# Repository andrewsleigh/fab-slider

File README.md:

# Fab Slider

A fab-able DIY motorised camera slider

* [The (Arduino Nano) microcontroller, user controls and TMC2130 stepper driver are all integrated onto one board here](boards/driver-arduino-shield/v3)
* [3D and 2D files for the assembly are all here](3d-parts/v1)
* [Arduino sketch here](arduino-code/v2)

This project is designed to be easily replicated, adapted or hacked on by anyone with access to typical fablab tools. 

It's primarily an exercise in learning: how to use a 3D printer; how use an Arduino; how to design circuit boards; how to assemble a machine, and so on. 

So really, it's all about the documentation, which is here:

* <https://andrewsleigh.com/fab-slider/>
* Or see [`docs/_posts/`](docs/_posts/) in this repo

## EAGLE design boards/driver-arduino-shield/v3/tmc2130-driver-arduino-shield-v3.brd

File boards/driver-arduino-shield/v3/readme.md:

# Readme

<!--  -->

This is version 3 of a board to use a stepper driver (a TMC2130) with an Arduino Uno to control a stepper motor for a <a href="https://andrewsleigh.com/fab-slider/">camera slider</a>.

The front (copper side) of the board, with all traces and user-facing components:

The back side of the board, which just has female headers for the Nano and driver module, and male headers for connections to the motor and end stops:

(Not visible here is the smoothing capacitor underneath the driver module.)

## Layout diagrams

### Front

### Back

This is the release version of the board design. It works with the release version of the Arduino code at [../../../arduino-code/v2](../../../arduino-code/v2).

As well as the passive components, you'll need an Arduino Nano, an I2C 128x64 OLED module and a TMC2130 stepper driver. The code could be adapted to work with an A4988-based driver, which should be compatible with this board.

The full story of how I came to this board design is documented in the [journal](https://andrewsleigh.com/fab-slider/), in particular:

* [Designing a new stepper driver and controls board](https://andrewsleigh.com/fab-slider/v2-shield/) (v2)
* [Designing a new board — again](https://andrewsleigh.com/fab-slider/v3-shield/) (v3)

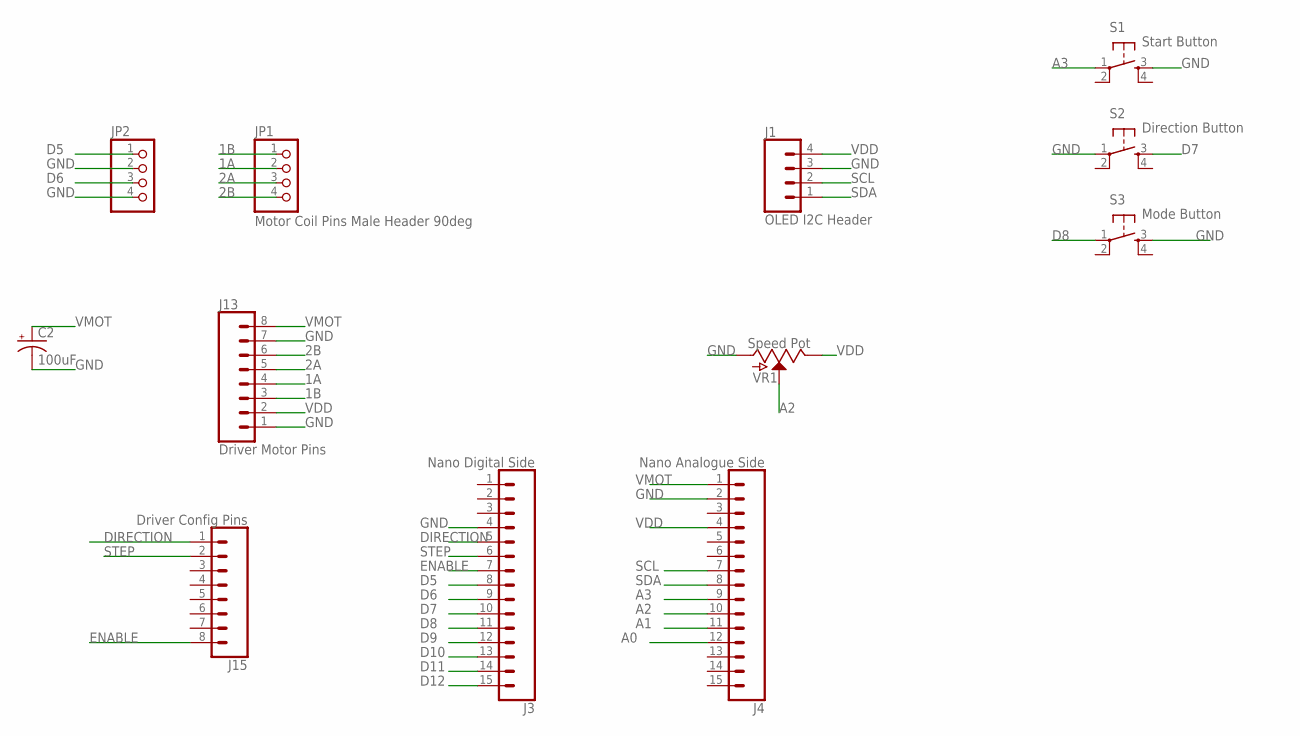
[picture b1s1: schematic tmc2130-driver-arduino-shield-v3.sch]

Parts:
C2: 100uF; CPOL-RADIAL-2.5MM-6.5MM
J1: OLED I2C Header; 1X04_LONGPADS
J3: Nano Digital Side; 1X15
J4: Nano Analogue Side; 1X15
J13: Driver Motor Pins; 1X08_LONGPADS
J15: Driver Config Pins; 1X08_LONGPADS
JP1: Motor Coil Pins Male Header 90deg; 1X04/90
JP2: PINHD-1X4/90; 1X04/90
S1: Start Button; 6MM_SWITCH
S2: Direction Button; 6MM_SWITCH
S3: Mode Button; 6MM_SWITCH
VR1: Speed Pot; POT-PTH-ALPS

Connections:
1A: J13.4, JP1.2
1B: J13.3, JP1.1
2A: J13.5, JP1.3
2B: J13.6, JP1.4
A0: J4.12
A1: J4.11
A2: J4.10, VR1.P$2 (S)
A3: J4.9, S1.1
D5: J3.8, JP2.1
D6: J3.9, JP2.3
D7: J3.10, S2.3 (S)
D8: J3.11, S3.1
D9: J3.12
D10: J3.13
D11: J3.14
D12: J3.15
DIRECTION: J3.5, J15.1
ENABLE: J3.7, J15.8
GND: C2.2 (-), J1.3, J3.4, J4.2, J13.1, J13.7, JP2.2, JP2.4, S1.3 (S), S2.1, S3.3 (S), VR1.P$3 (A)
SCL: J1.2, J4.7
SDA: J1.1, J4.8
STEP: J3.6, J15.2
VDD: J1.4, J4.4, J13.2, VR1.P$1 (E)
VMOT: C2.1 (+), J4.1, J13.8

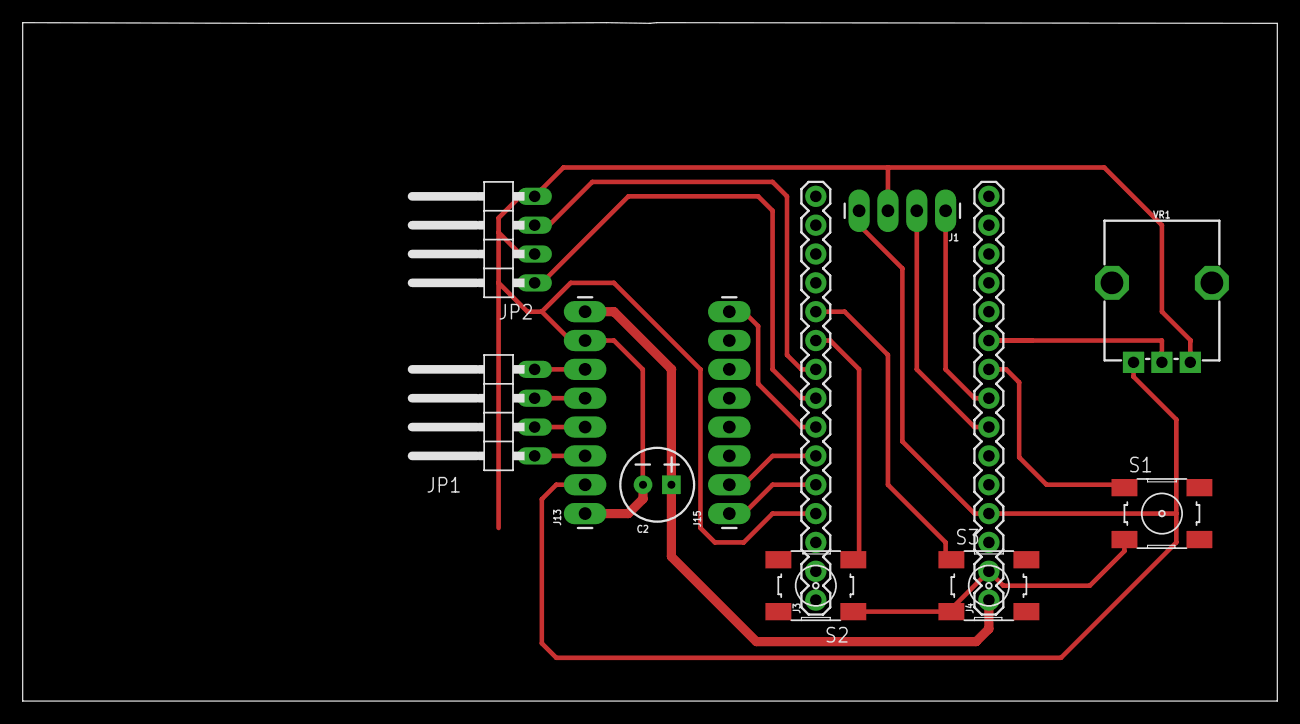
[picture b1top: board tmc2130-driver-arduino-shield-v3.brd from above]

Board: 2 copper layers, 110.5 x 59.7 mm, 12 parts (0 on the bottom side), 18 nets.

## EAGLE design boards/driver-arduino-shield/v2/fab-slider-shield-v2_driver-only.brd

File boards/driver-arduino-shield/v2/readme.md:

# Readme

This is version 2 of a board to use a stepper driver (a TMC2130) with an Arduino Uno to control a stepper motor for a <a href="https://andrewsleigh.com/fab-slider/">camera slider</a>.

The board is in two parts for easier mounting. This diagram shows how they're connected. The pins on the right are to connect to the motor and endstops which are assumed for this design to be outside of the housing for the boards.

This board design is documented in much more detail in my journal here:

<https://andrewsleigh.com/fab-slider/v2-shield/>

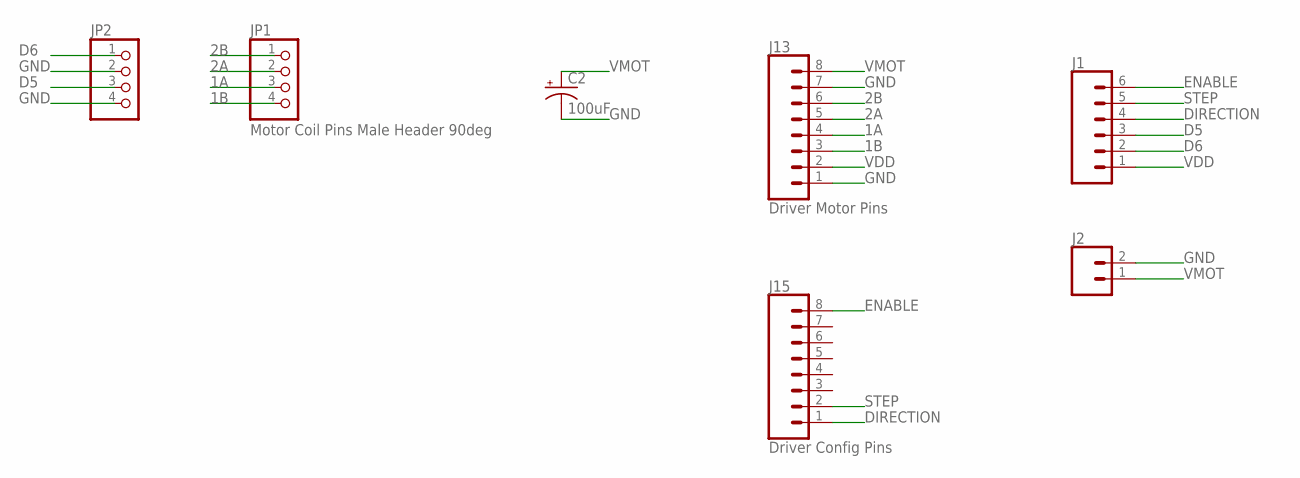
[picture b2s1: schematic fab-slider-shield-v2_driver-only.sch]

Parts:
C2: 100uF; CPOL-RADIAL-2.5MM-6.5MM
J1: CONN_06LONGPADS; 1X06_LONGPADS
J2: CONN_02PTH3; 1X02_LONGPADS
J13: Driver Motor Pins; 1X08_LONGPADS
J15: Driver Config Pins; 1X08_LONGPADS
JP1: Motor Coil Pins Male Header 90deg; 1X04/90
JP2: PINHD-1X4/90; 1X04/90

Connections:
1A: J13.4, JP1.3
1B: J13.3, JP1.4
2A: J13.5, JP1.2
2B: J13.6, JP1.1
D5: J1.3, JP2.3
D6: J1.2, JP2.1
DIRECTION: J1.4, J15.1
ENABLE: J1.6, J15.8
GND: C2.2 (-), J2.2, J13.1, J13.7, JP2.2, JP2.4
STEP: J1.5, J15.2
VDD: J1.1, J13.2
VMOT: C2.1 (+), J2.1, J13.8

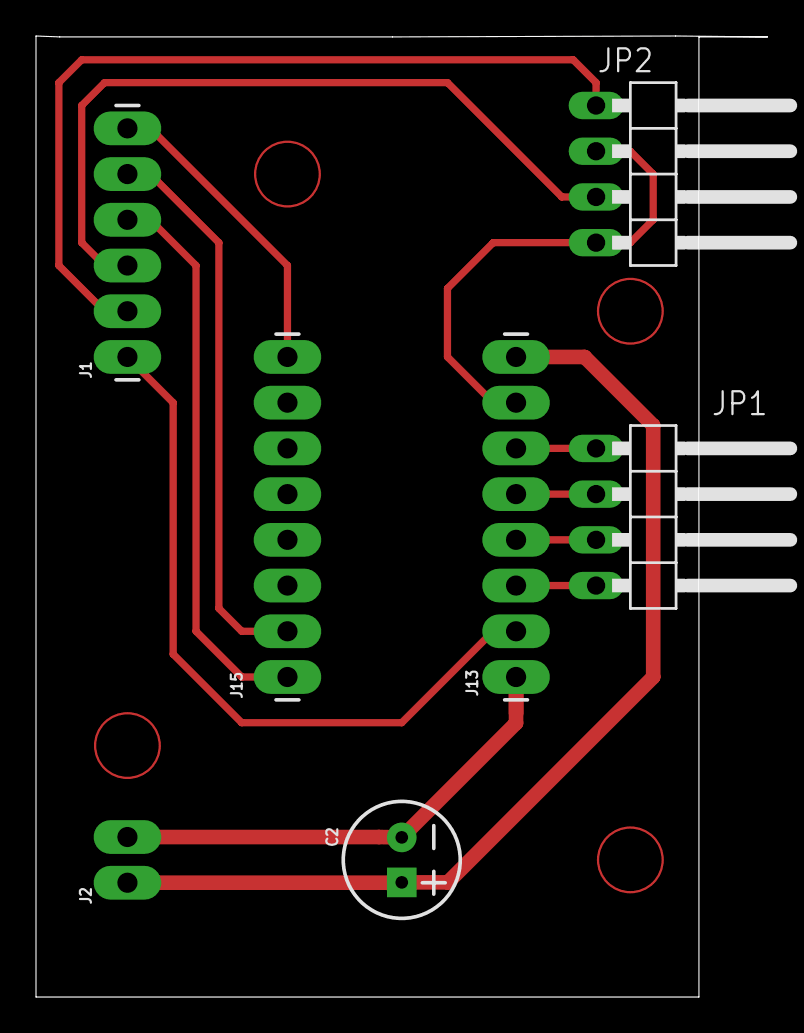
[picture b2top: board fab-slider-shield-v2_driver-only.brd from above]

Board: 2 copper layers, 40.6 x 53.4 mm, 7 parts (0 on the bottom side), 12 nets.

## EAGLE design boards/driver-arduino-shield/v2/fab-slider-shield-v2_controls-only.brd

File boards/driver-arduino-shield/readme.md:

# Readme

This is a simple shield to mount an A4988 stepper driver board onto an Arduino Uno giving easy access to the configuration pins, connections to the motor, and also separate breakouts to attach switches and analogue inputs for motion control

Features:
* Mounting headers for a standard 'Stepstick'-style A4988 stepper motor driver
* Routes DIRECTION to Arduino pin D3, and STEP to Arduino pin D2
* Through-board male-female headers to fit an Arduino Uno R3
* 4 pin header breaking out pins 1B, 1A, 2A, 2B (reading left-right) to wire up to motor
* 3 pin header breaking out VDD line, so MS1, MS2, and MS3 can be pulled high to use micro-stepping modes
* 6 pin header breaking out the main driver configuration pins: SLEEP, RESET, MS3, MS2, MS1, ENABLE (reading left-right)
* One header to accept up to 3 digital inputs from buttons or end-stops (to Arduino I/O pins D10, D9, D8, reading top-bottom)
* One header to accept up to three analogue inputs for example from potentiometers (to Arduino I/O pins A2, A1, A0, reading top-bottom)

## Connecting the motor

The header labelled "Motor Pins" directly below the driver mounting headers is designed to take a 4-pin female-terminated motor cable. Left to right, the pins are: 1B, 1A, 2A, 2B.

## Using micro-stepping modes

The A4988 datasheet includes a truth table to show how you can access micro-step resolution down to 1/16 step. The pins have internal pull-down resistors, so you can activate each pin by connecting it to VDD. The MS1-3 pins are broken out directly from the board to the header above it ("Driver Config Pins"). There are 3 pins all connected to VDD on one header ("VDD MS Pins") next to the motor pin header. Use jumper wires to connect these to the micro-stepping pins, and access these modes.

|  MS1  |  MS2  |  MS3  | Microstep Resolution | Excitation Mode |
| :---: | :---: | :---: | :------------------: | :-------------: |
|   L   |   L   |   L   |      Full Step       |     2 Phase     |
|   H   |   L   |   L   |      Half Step       |    1-2 Phase    |
|   L   |   H   |   L   |     Quarter Step     |   W1-2 Phase    |
|   H   |   H   |   L   |     Eighth Step      |   2W1-2 Phase   |
|   H   |   H   |   H   |    Sixteenth Step    |   4W1-2 Phase   |

## Using – or not using – sleep and reset modes

The SLEEP and RESET pins can be used to enter different modes (detailed in the datasheet). If you're not using these modes, and therefore not connecting the pins, they have a floating voltage and can cause problems. If you're not using these mode, connect these two pins with a wire to pull them both high.

## External inputs

As well as the pins for the driver itself, there are two header to allow other components to be connected more easily.

### Using the digital inputs

These inputs connect one side of the switch to GND, the other to the input pin. So you should set the internal pull-up resistor in your code to use them:

```
pinMode(10, INPUT_PULLUP);
pinMode(9, INPUT_PULLUP);
pinMode(8, INPUT_PULLUP);
```

Note the comments below ("Unused header pins") about the arrangement on pins on this header.  Specifically, the top pin is not used.

#### Digital inputs pin table (top-bottom)

|  Pin  | Connection |
| :-----: | :------: |
|    1    | (unused) |
| **Input 1** |      |
|    2    |   D10    |
|    3    | (unused) |
|    4    |   GND    |
| **Input 2** |      |
|    5    |    D9    |
|    6    | (unused) |
|    7    |   GND    |
| **Input 3** |      |
|    8    |    D8    |
|    9    | (unused) |
|   10    |   GND    |

### Using the analogue inputs

There are 3 sets of 3 pins to allow the connection of 3 analogue inputs. Each set is wired up (top-bottom) VDD – Analogue input – GND. The analogue inputs used are (top-bottom) A2, A1, A0.

Note the comments below about the arrangement on pins on this header. Specifically, the top pin is not used.

#### Analogue inputs pin table (top-bottom)

|  Pin  | Connection |
| :---: | :------: |
|   1   | (unused) |
| **Input 1** |    |
|   2   |   VDD    |
|   3   |    A2    |
|   4   |   GND    |
| **Input 2** |    |
|   5   |   VDD    |
|   6   |    A1    |
|   7   |   GND    |
| **Input 3** |    |
|   8   |   VDD    |
|  19   |    A0    |
|  10   |   GND    |

## Unused header pins

The driver is mounted on the left-most 8 pins of the dual 10-pin headers in the centre of the board (DIRECTION pin top-left). Ignore the two pins at the right of each header.

Analogue and digital inputs are connected in 3 sets of 3 pins each. This might be a slightly odd arrangement for the digital inputs, which only need two signals, but I'm using these for my end-stop switches, which have three terminals, and I want maximum flexibility in how I connect them. This is likely to change in a future version. Ignore the top pin of each of these headers.

The choice of header on this board is largely driven by what I have available to me: 10-pin SMD female headers, and 6-pin through-board female headers. That's why there are unused pins on some of the headers, and why not all of the Arduino pins are exposed through the shield. If you have a better selection of headers, feel free to adjust this design.

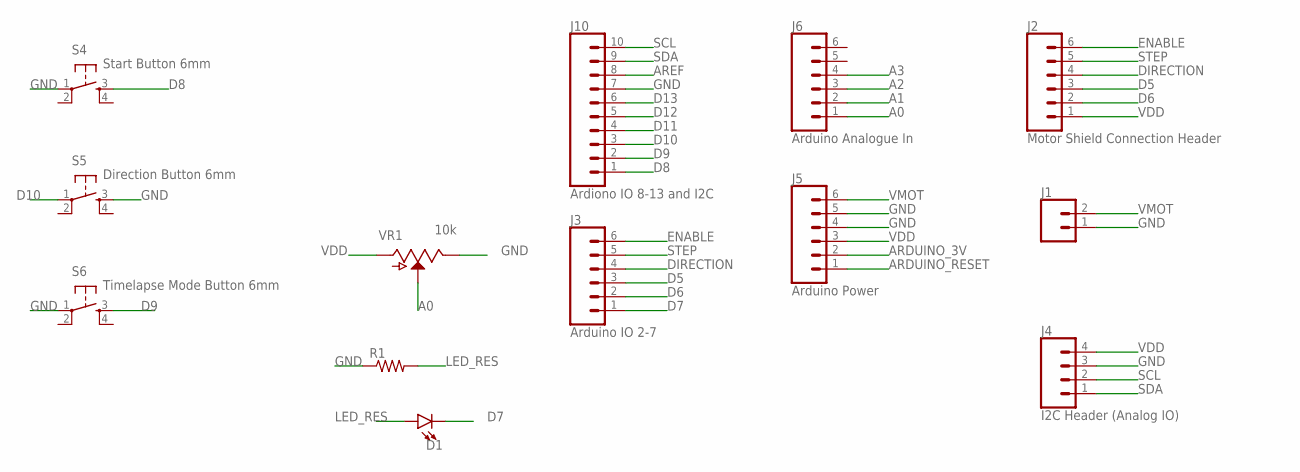
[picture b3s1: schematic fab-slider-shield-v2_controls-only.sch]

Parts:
D1: LED1206; LED-1206
J1: CONN_02PTH3; 1X02_LONGPADS
J2: Motor Shield Connection Header; 1X06_LONGPADS
J3: Arduino IO 2-7; 1X06_NO_SILK
J4: I2C Header (Analog IO); 1X04
J5: Arduino Power; 1X06_NO_SILK
J6: Arduino Analogue In; 1X06_NO_SILK
J10: Ardiono IO 8-13 and I2C; 1X10_NO_SILK
R1: RES-US1206FAB; R1206FAB
S4: Start Button 6mm; 6MM_SWITCH
S5: Direction Button 6mm; 6MM_SWITCH
S6: Timelapse Mode Button 6mm; 6MM_SWITCH
VR1: 10k; POT-PTH-ALPS

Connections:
A0: J6.1, VR1.P$2 (S)
A1: J6.2
A2: J6.3
A3: J6.4
ARDUINO_3V: J5.2
ARDUINO_RESET: J5.1
AREF: J10.8
D5: J2.3, J3.3
D6: J2.2, J3.2
D7: D1.C, J3.1
D8: J10.1, S4.3 (S)
D9: J10.2, S6.3 (S)
D10: J10.3, S5.1
D11: J10.4
D12: J10.5
D13: J10.6
DIRECTION: J2.4, J3.4
ENABLE: J2.6, J3.6
GND: J1.1, J4.3, J5.4, J5.5, J10.7, R1.1, S4.1, S5.3 (S), S6.1, VR1.P$1 (E)
LED_RES: D1.A, R1.2
SCL: J4.2, J10.10
SDA: J4.1, J10.9
STEP: J2.5, J3.5
VDD: J2.1, J4.4, J5.3, VR1.P$3 (A)
VMOT: J1.2, J5.6

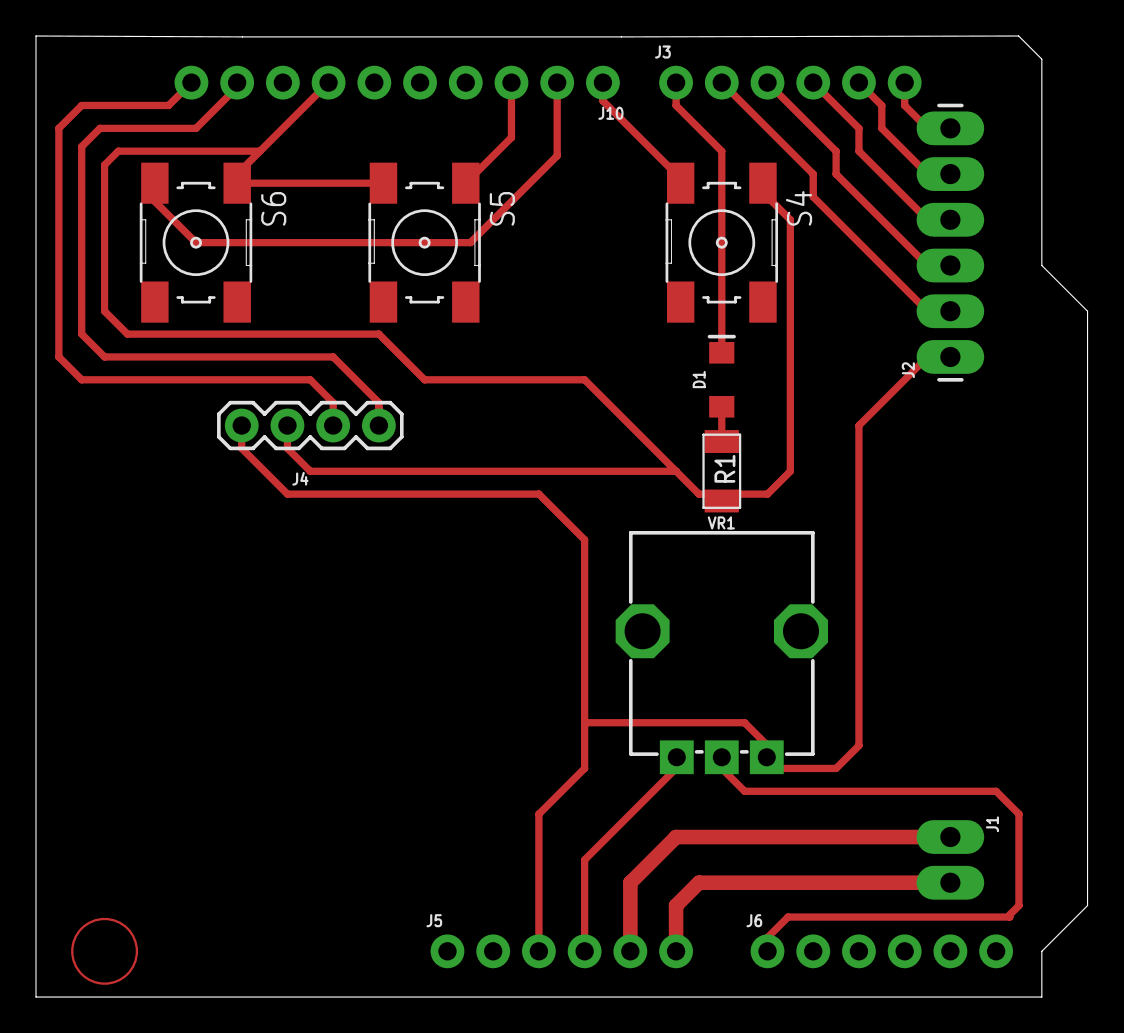
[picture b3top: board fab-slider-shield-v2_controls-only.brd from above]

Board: 2 copper layers, 58.4 x 53.4 mm, 13 parts (0 on the bottom side), 16 nets.

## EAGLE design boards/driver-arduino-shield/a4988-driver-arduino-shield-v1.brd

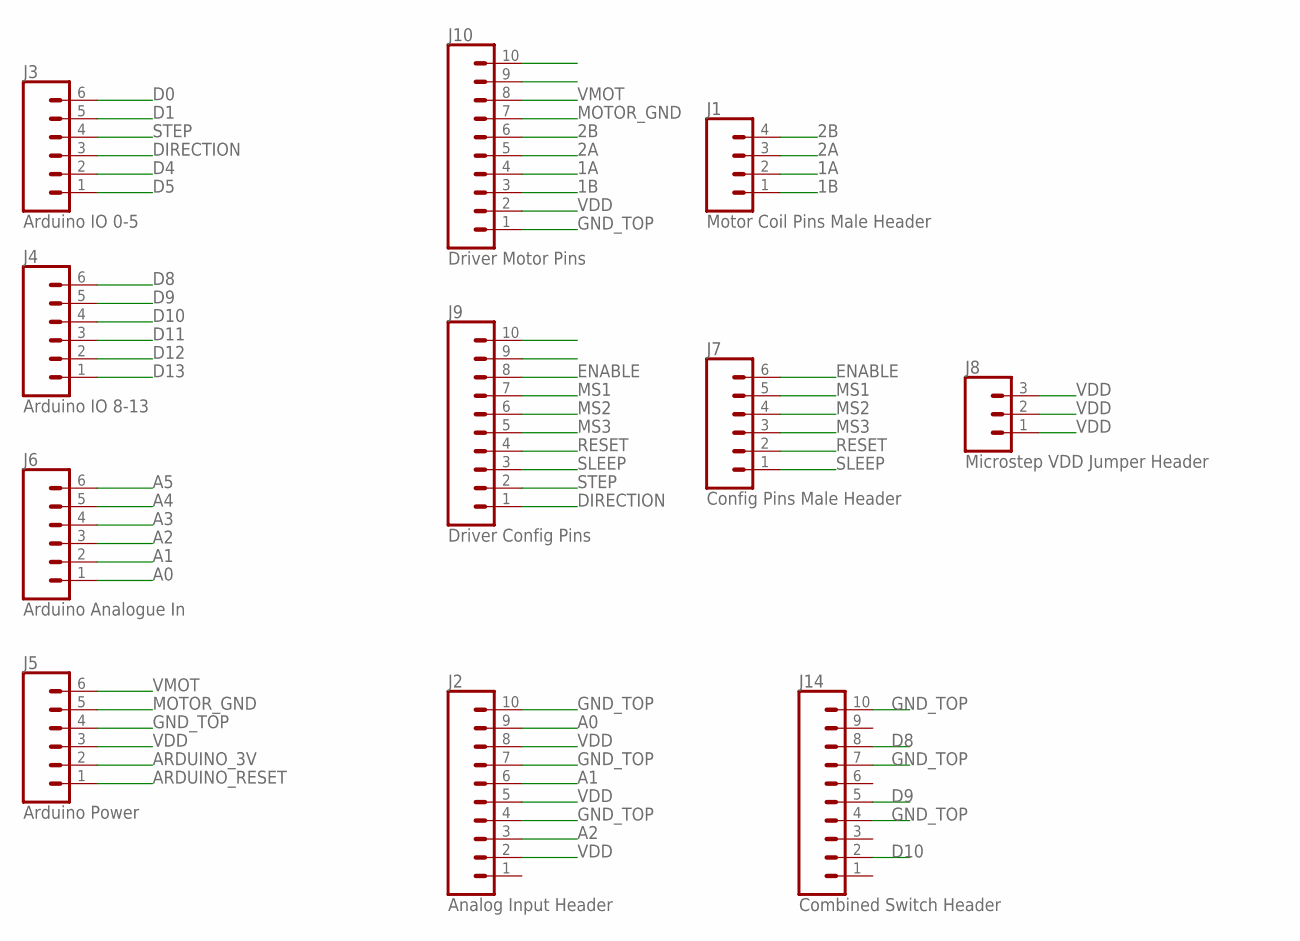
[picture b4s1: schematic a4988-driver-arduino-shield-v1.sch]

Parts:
J1: Motor Coil Pins Male Header; 1X04_LONGPADS
J2: Analog Input Header; 1X10_SMD_MALE
J3: Arduino IO 0-5; 1X06_NO_SILK
J4: Arduino IO 8-13; 1X06_NO_SILK
J5: Arduino Power; 1X06_NO_SILK
J6: Arduino Analogue In; 1X06_NO_SILK
J7: Config Pins Male Header; 1X06_SMD_MALE
J8: Microstep VDD Jumper Header; 1X03_LONGPADS
J9: Driver Config Pins; 1X10_SMD_MALE
J10: Driver Motor Pins; 1X10_SMD_MALE
J14: Combined Switch Header; 1X10_SMD_MALE

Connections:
1A: J1.2, J10.4
1B: J1.1, J10.3
2A: J1.3, J10.5
2B: J1.4, J10.6
A0: J2.9, J6.1
A1: J2.6, J6.2
A2: J2.3, J6.3
A3: J6.4
A4: J6.5
A5: J6.6
ARDUINO_3V: J5.2
ARDUINO_RESET: J5.1
D0: J3.6
D1: J3.5
D4: J3.2
D5: J3.1
D8: J4.6, J14.8
D9: J4.5, J14.5
D10: J4.4, J14.2
D11: J4.3
D12: J4.2
D13: J4.1
DIRECTION: J3.3, J9.1
ENABLE: J7.6, J9.8
GND_TOP: J2.4, J2.7, J2.10, J5.4, J10.1, J14.4, J14.7, J14.10
MOTOR_GND: J5.5, J10.7
MS1: J7.5, J9.7
MS2: J7.4, J9.6
MS3: J7.3, J9.5
RESET: J7.2, J9.4
SLEEP: J7.1, J9.3
STEP: J3.4, J9.2
VDD: J2.2, J2.5, J2.8, J5.3, J8.1, J8.2, J8.3, J10.2
VMOT: J5.6, J10.8

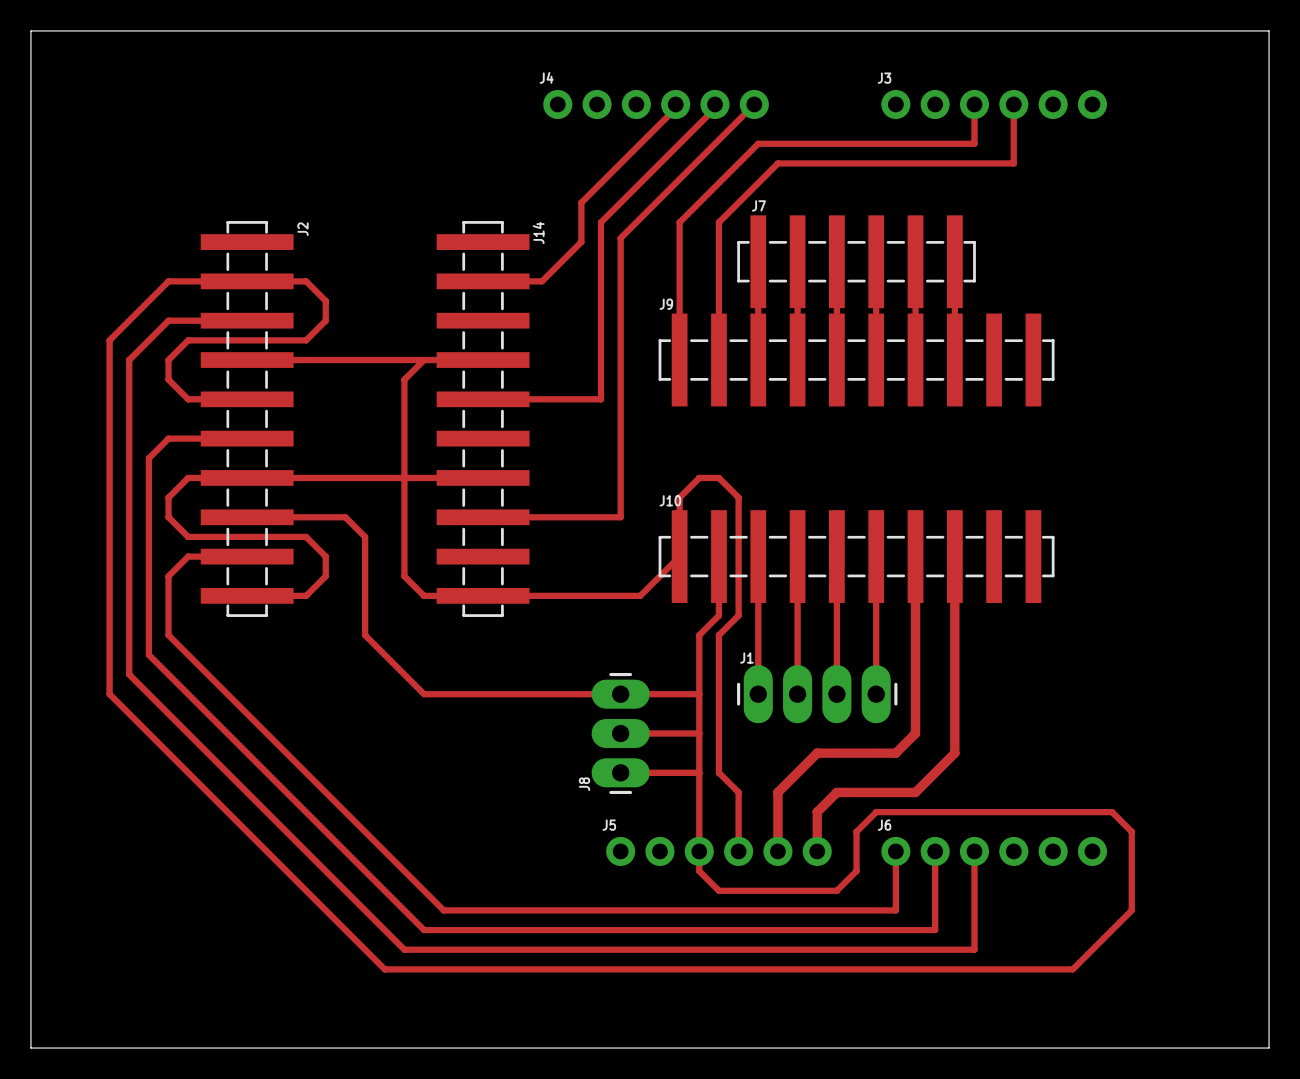
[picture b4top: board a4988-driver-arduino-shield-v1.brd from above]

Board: 2 copper layers, 80.0 x 65.7 mm, 11 parts (0 on the bottom side), 22 nets.

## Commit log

2019-04-12 intro
2019-04-12 jekyll init
2019-04-12 mostly config
2019-04-12 add images
2019-04-12 split intro page up
2019-04-12 permalinks in frontmatter
2019-04-12 text fixes
2019-04-12 remove permalinks
2019-04-12 remove colons in fm
2019-04-12 permalinks back again
2019-04-12 url fixes
2019-04-12 started looking at main components
2019-04-12 Update 2019-04-12-design-1-main-components.md
    double space line breaks
2019-04-12 mostly design updates
2019-04-13 Design 1
2019-04-14 more work on design page
2019-04-27 V1 board design for driver shield
2019-04-27 add supplementary files for driver shield
2019-04-28 board pictures
2019-04-28 add gantry 3D parts
2019-04-28 add 3d parts
2019-04-28 tidy 3D parts
2019-04-28 add end stop clip
2019-04-28 Add 2D files for idler pulley plate
2019-04-30 add motor bracket
2019-04-30 add assembly files
2019-04-30 update post indexing
2019-04-30 home layout
2019-04-30 page ordering
2019-04-30 sort_id
2019-04-30 journal updates
2019-04-30 journal
2019-04-30 urls
2019-04-30 endstops
2019-04-30 endstop assets
2019-04-30 making v1
2019-05-04 start building page
2019-05-04 motor bracket docs
2019-05-04 building mods
2019-05-11 add code for complex state machine
2019-05-11 add state machine diagram and readme
2019-05-11 state machine blog posts
2019-05-22 Accelstepper
2019-05-22 Update accelstepper
2019-05-22 <# Enter your message here. #>
2019-05-22 AccellStepper changes
2019-05-22 update current adjustments
2019-05-30 move 3d parts readme
2019-05-30 move boards into v1/
2019-05-30 move more board files into v1/
2019-05-30 new homepage template
2019-05-30 new post titles
2019-06-02 add v1 review
2019-07-17 add tmc2130 driver page
2019-07-18 Add v2 shield designs
2019-07-18 update shield design page and assets
2019-07-18 readme changes
2019-08-05 code readme
2019-08-05 add faceplate files
2019-08-05 Add v3 shield design
2019-08-05 add hero image
2019-08-09 board diagrams, oled mount, photos
2019-08-09 board v3 photos
2019-08-09 new blog posts
2019-08-09 arduino readmes
2019-08-14 Update homepage
2019-08-15 Add results page
2019-08-17 Add v 2.1 code
2019-08-22 Bump nokogiri from 1.10.2 to 1.10.4
    Bumps [nokogiri](https://github.com/sparklemotion/nokogiri) from 1.10.2 to 1.10.4.
    - [Release notes](https://github.com/sparklemotion/nokogiri/releases)
    - [Changelog](https://github.com/sparklemotion/nokogiri/blob/master/CHANGELOG.md)
    - [Commits](https://github.com/sparklemotion/nokogiri/compare/v1.10.2...v1.10.4)
2019-11-27 Bump rubyzip from 1.2.2 to 2.0.0
    Bumps [rubyzip](https://github.com/rubyzip/rubyzip) from 1.2.2 to 2.0.0.
    - [Release notes](https://github.com/rubyzip/rubyzip/releases)
    - [Changelog](https://github.com/rubyzip/rubyzip/blob/master/Changelog.md)
    - [Commits](https://github.com/rubyzip/rubyzip/compare/v1.2.2...v2.0.0)
2020-02-25 Bump nokogiri from 1.10.4 to 1.10.8
    Bumps [nokogiri](https://github.com/sparklemotion/nokogiri) from 1.10.4 to 1.10.8.
    - [Release notes](https://github.com/sparklemotion/nokogiri/releases)
    - [Changelog](https://github.com/sparklemotion/nokogiri/blob/master/CHANGELOG.md)
    - [Commits](https://github.com/sparklemotion/nokogiri/compare/v1.10.4...v1.10.8)
2021-05-20 Bump nokogiri from 1.10.4 to 1.11.4
    Bumps [nokogiri](https://github.com/sparklemotion/nokogiri) from 1.10.4 to 1.11.4.
    - [Release notes](https://github.com/sparklemotion/nokogiri/releases)
    - [Changelog](https://github.com/sparklemotion/nokogiri/blob/main/CHANGELOG.md)
    - [Commits](https://github.com/sparklemotion/nokogiri/compare/v1.10.4...v1.11.4)
2021-07-13 Bump addressable from 2.5.2 to 2.8.0
    Bumps [addressable](https://github.com/sporkmonger/addressable) from 2.5.2 to 2.8.0.
    - [Release notes](https://github.com/sporkmonger/addressable/releases)
    - [Changelog](https://github.com/sporkmonger/addressable/blob/main/CHANGELOG.md)
    - [Commits](https://github.com/sporkmonger/addressable/compare/addressable-2.5.2...addressable-2.8.0)
    ---
    updated-dependencies:
2021-09-27 Bump nokogiri from 1.10.4 to 1.12.5
    Bumps [nokogiri](https://github.com/sparklemotion/nokogiri) from 1.10.4 to 1.12.5.
    - [Release notes](https://github.com/sparklemotion/nokogiri/releases)
    - [Changelog](https://github.com/sparklemotion/nokogiri/blob/main/CHANGELOG.md)
    - [Commits](https://github.com/sparklemotion/nokogiri/compare/v1.10.4...v1.12.5)
    ---
    updated-dependencies:
2022-02-26 Bump nokogiri from 1.10.4 to 1.13.3
    Bumps [nokogiri](https://github.com/sparklemotion/nokogiri) from 1.10.4 to 1.13.3.
    - [Release notes](https://github.com/sparklemotion/nokogiri/releases)
    - [Changelog](https://github.com/sparklemotion/nokogiri/blob/main/CHANGELOG.md)
    - [Commits](https://github.com/sparklemotion/nokogiri/compare/v1.10.4...v1.13.3)
    ---
    updated-dependencies:
2022-04-12 Bump nokogiri from 1.10.4 to 1.13.4
    Bumps [nokogiri](https://github.com/sparklemotion/nokogiri) from 1.10.4 to 1.13.4.
    - [Release notes](https://github.com/sparklemotion/nokogiri/releases)
    - [Changelog](https://github.com/sparklemotion/nokogiri/blob/v1.13.4/CHANGELOG.md)
    - [Commits](https://github.com/sparklemotion/nokogiri/compare/v1.10.4...v1.13.4)
    ---
    updated-dependencies:
2022-05-18 Bump nokogiri from 1.10.4 to 1.13.6
    Bumps [nokogiri](https://github.com/sparklemotion/nokogiri) from 1.10.4 to 1.13.6.
    - [Release notes](https://github.com/sparklemotion/nokogiri/releases)
    - [Changelog](https://github.com/sparklemotion/nokogiri/blob/main/CHANGELOG.md)
    - [Commits](https://github.com/sparklemotion/nokogiri/compare/v1.10.4...v1.13.6)
    ---
    updated-dependencies:
2022-07-22 Bump tzinfo from 1.2.5 to 1.2.10
    Bumps [tzinfo](https://github.com/tzinfo/tzinfo) from 1.2.5 to 1.2.10.
    - [Release notes](https://github.com/tzinfo/tzinfo/releases)
    - [Changelog](https://github.com/tzinfo/tzinfo/blob/master/CHANGES.md)
    - [Commits](https://github.com/tzinfo/tzinfo/compare/v1.2.5...v1.2.10)
    ---
    updated-dependencies:
2022-10-06 Bump addressable from 2.5.2 to 2.8.1
    Bumps [addressable](https://github.com/sporkmonger/addressable) from 2.5.2 to 2.8.1.
    - [Release notes](https://github.com/sporkmonger/addressable/releases)
    - [Changelog](https://github.com/sporkmonger/addressable/blob/main/CHANGELOG.md)
    - [Commits](https://github.com/sporkmonger/addressable/compare/addressable-2.5.2...addressable-2.8.1)
    ---
    updated-dependencies:

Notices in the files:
parts and their libraries:
SparkFun-Connectors: Licensing: Creative Commons ShareAlike 4.0 International - https://creativecommons.org/licenses/by-sa/4.0
